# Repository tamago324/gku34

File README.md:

# gku34

* 狭ピッチ
  * キーピッチが縦17mmx横18mm
* KiCad 6 で作成
* [horizon プラグイン](https://github.com/skarrmann/horizon/blob/5833ec133d5f8fa4f3824622efd5dbfc89d797ec/kicad-plugins/horizon-board-producer-plugin.py)を使ってボトムプレートを生成
* choc v1 (rev0.1, rev0.2)
* Lofree switch (rev0.3)

## LICENSE

<br />この作品は <a rel="license" href="http://creativecommons.org/licenses/by/4.0/">クリエイティブ・コモンズ 表示 4.0 国際 ライセンス</a>の下に提供されています。

> 共有 — どのようなメディアやフォーマットでも資料を複製したり、再配布できます。
> 
> 翻案 — マテリアルをリミックスしたり、改変したり、別の作品のベースにしたりできます。営利目的も含め、どのような目的でも。

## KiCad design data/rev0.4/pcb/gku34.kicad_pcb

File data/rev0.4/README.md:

* [Lofree スイッチ](https://www.lofree.co/products/lofree-x-kailh-full-pom-low-profile-switches)を使えるようにした
  * Choc V1 も使える
* rev0.3 との違い
  * 配線をF.cu側に集めた
    * スイッチの交換をするときに、配線に傷がつかないようにするため

## 発注するとき (JLCPCB)

* 基板
  * main_pcb (メイン基板)
    * `gerbers/main_pcb/gku34_247.632052x114.711068mm_for_JLCPCB.zip`
      * PCB Thickness: 1.6mm
      * Remove Order Number: Specify a location
  * bottom_plate (ボトムプレート)
    * `gerbers/bottom_plate/gku34-bottom-plate_247.632052x114.711068mm_for_JLCPCB.zip`
      * PCB Thickness: 1.6mm
      * Remove Order Number: Specify a location
* トッププレート
  * `stl/gku34-top-plate-jlcpcb.stl`
    * 3D Technology: MJF(Nylon)
    * Material: PA12-HP Nylon
    * Color: Black

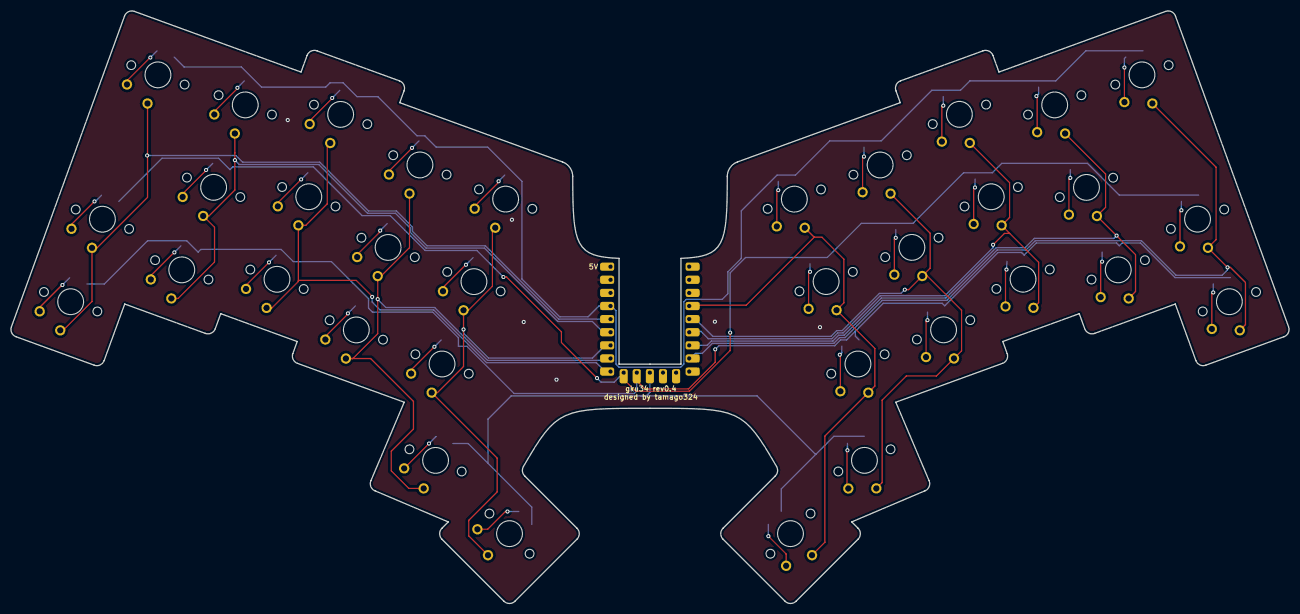
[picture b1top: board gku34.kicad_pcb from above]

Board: 2 copper layers, 247.6 x 114.8 mm, 69 parts (0 on the bottom side), 48 nets.

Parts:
D1, D2, D3, D4, D5, D6, D7, D8, D9, D10, D11, D12, D13, D14, D15, D16, D17, D18, D19, D20, D21, D22, D23, D24, D25, D26, D27, D28, D29, D30, D31, D32, D33, D34: D; Diode_SMD
RZ1: RP2040-Zero
SW1, SW2, SW3, SW4, SW5, SW6, SW7, SW8, SW9, SW11, SW12, SW13, SW14, SW15, SW16, SW17, SW18, SW19, SW20, SW21, SW22, SW23, SW24, SW25, SW26, SW27, SW28, SW29, SW30, SW31, SW32, SW33, SW34: SW_PUSH; SW_Choc_V2
SWe: SW_PUSH; SW_Choc_V2

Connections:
unnamed: D1.2 (A), SW1.2
unnamed: D2.2 (A), SW2.2
unnamed: D3.2 (A), SW3.2
unnamed: D4.2 (A), SW4.2
unnamed: D5.2 (A), SW5.2
unnamed: D6.2 (A), SW6.2
unnamed: D7.2 (A), SW7.2
unnamed: D8.2 (A), SW8.2
unnamed: D9.2 (A), SW9.2
unnamed: D10.2 (A), SWe.2
unnamed: D11.2 (A), SW11.2
unnamed: D12.2 (A), SW12.2
unnamed: D13.2 (A), SW13.2
unnamed: D14.2 (A), SW14.2
unnamed: D15.2 (A), SW15.2
unnamed: D16.2 (A), SW16.2
unnamed: D17.2 (A), SW17.2
unnamed: D18.2 (A), SW18.2
unnamed: D19.2 (A), SW19.2
unnamed: D20.2 (A), SW20.2
unnamed: D21.2 (A), SW21.2
unnamed: D22.2 (A), SW22.2
unnamed: D23.2 (A), SW23.2
unnamed: D24.2 (A), SW24.2
unnamed: D25.2 (A), SW25.2
unnamed: D26.2 (A), SW26.2
unnamed: D27.2 (A), SW27.2
unnamed: D28.2 (A), SW28.2
unnamed: D29.2 (A), SW29.2
unnamed: D30.2 (A), SW30.2
unnamed: D31.2 (A), SW31.2
unnamed: D32.2 (A), SW32.2
unnamed: D33.2 (A), SW33.2
unnamed: D34.2 (A), SW34.2
col0: RZ1.19 (GP28), SW1.1, SW11.1, SW21.1
col1: RZ1.18 (GP27), SW2.1, SW12.1, SW22.1
col2: RZ1.15 (GP14), SW3.1, SW13.1, SW23.1
col3: RZ1.16 (GP15), SW4.1, SW14.1, SW24.1, SW31.1
col4: RZ1.17 (GP26), SW5.1, SW15.1, SW25.1, SW32.1
col5: RZ1.4 (GP3), SW6.1, SW16.1, SW26.1, SW33.1
col6: RZ1.5 (GP4), SW7.1, SW17.1, SW27.1, SW34.1
col7: RZ1.6 (GP5), SW8.1, SW18.1, SW28.1
col8: RZ1.7 (GP6), SW9.1, SW19.1, SW29.1
col9: RZ1.8 (GP7), SW20.1, SW30.1, SWe.1
row0: D1.1 (K), D2.1 (K), D3.1 (K), D4.1 (K), D5.1 (K), D6.1 (K), D7.1 (K), D8.1 (K), D9.1 (K), D10.1 (K), RZ1.20 (GP29)
row1: D11.1 (K), D12.1 (K), D13.1 (K), D14.1 (K), D15.1 (K), D16.1 (K), D17.1 (K), D18.1 (K), D19.1 (K), D20.1 (K), RZ1.14 (GP13)
row2: D21.1 (K), D22.1 (K), D23.1 (K), D24.1 (K), D25.1 (K), D26.1 (K), D27.1 (K), D28.1 (K), D29.1 (K), D30.1 (K), RZ1.13 (GP12)
row3: D31.1 (K), D32.1 (K), D33.1 (K), D34.1 (K), RZ1.12 (GP11)

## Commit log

2023-07-08 init
2023-07-17 update top-plate
2023-07-21 add rev0.2
2023-07-21 add README.md
2023-07-22 add vial firmware
2023-07-23 update buildguide
2023-07-29 add rev 0.2
2023-07-29 fix top plate stl file
2023-08-09 add: jlcpcb top-plate
2023-08-11 update uf2
2024-03-19 rev0.3 を追加
2024-03-19 ドキュメントの更新
2024-03-19 おすすめキーキャップについて追記
2024-03-19 update README
2024-03-20 add README
2024-03-25 rev0.4追加
2024-04-03 update vial_firmware
    QとE を押すことで unlock できるように対応
2024-04-03 マウスキーを有効化
2024-04-03 EXTRAKEY_ENABLE = yes

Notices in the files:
README.md:
CC BY 4.0
